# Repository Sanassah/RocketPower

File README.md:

# RocketPower

**An active fin control flight computer for model rockets.**

A model rocket built **from the ground up**: custom flight computer, custom PCB, active fin control for in-flight stabilization, and a full hardware-in-the-loop test rig.

**Status:** in bench and hardware-in-the-loop validation ahead of first flight.

---

## 🔧 Putting it together

<table><tr>
<td width="62%"></td>
<td width="38%"></td>
</tr></table>

---

## 🚀 What it does

- **Active fin control.** An ARM Cortex-M7 flight computer runs a PD controller on quaternion-derived tilt plus gyro rate, driving **4 independent servo fins** in real time for active stabilization during ascent.
- **Redundant recovery.** Apogee detection runs on multiple independent signals, each able to trigger deployment on its own.
- **Hardware-in-the-loop testing.** A custom 6DOF Simulink model drives the real flight computer over serial, so the control loop gets validated **before it ever has to fly**.
- **Custom PCB.** IMU, barometer, high-g accelerometer, GPS, power monitoring, pyro firing and continuity, and LoRa telemetry, all on one board.
- **Ground station.** A PyQt6 desktop app for live telemetry, 3D orientation, and command/control.

---

## 🧠 Architecture

Every sensor feeds one MCU; that MCU runs the active fin control law and drives every output.

```mermaid
flowchart TD
    classDef sensor fill:#4A90D9,stroke:#2C5F8A,color:#fff
    classDef compute fill:#F5A623,stroke:#B8780F,color:#000
    classDef output fill:#7ED321,stroke:#4C8A14,color:#000
    classDef ext fill:#9B59B6,stroke:#6C3483,color:#fff

    IMU[BNO085 IMU]:::sensor
    BARO[BMP390 Baro]:::sensor
    ACC[ADXL375 Accel]:::sensor
    GPS[ZOEM8 GPS]:::sensor
    PWR[INA260 Power]:::sensor

    subgraph MCU["ARM Cortex-M7 MCU (NXP i.MX RT1062)"]
        FSM[Flight State Machine]:::compute
        CTRL[PD Attitude Controller]:::compute
        PYRO[Pyro + Backup Deploy]:::compute
    end

    FINS[4x Servo Fins]:::output
    CHUTE[Recovery Parachute]:::output

    GS[GroundStation]:::ext
    SIM[Simulink 6DOF]:::ext

    IMU --> FSM
    BARO --> FSM
    ACC --> FSM
    GPS --> FSM
    PWR --> FSM
    FSM --> CTRL
    FSM --> PYRO
    CTRL --> FINS
    PYRO --> CHUTE
    FSM <-->|"LoRa, E22-900T22D"| GS
    FSM <-.->|"Serial, HITL only"| SIM

    style MCU fill:#FEF3E0,stroke:#F5A623,stroke-width:2px
```

---

## 🛠️ Hardware

Every subsystem on one custom board: IMU, barometer, high-g accelerometer, GPS, power monitoring, pyro firing/continuity, and telemetry.

---

## 🧪 Simulation and testing

Performance is modeled before anything is built, and the same model closes the loop with real hardware once it exists.

A full powered ascent, coast, and parachute deployment, run entirely in hardware-in-the-loop: **real flight computer, simulated flight.**

---

<p align="center"><sub>Where this is headed.</sub></p>

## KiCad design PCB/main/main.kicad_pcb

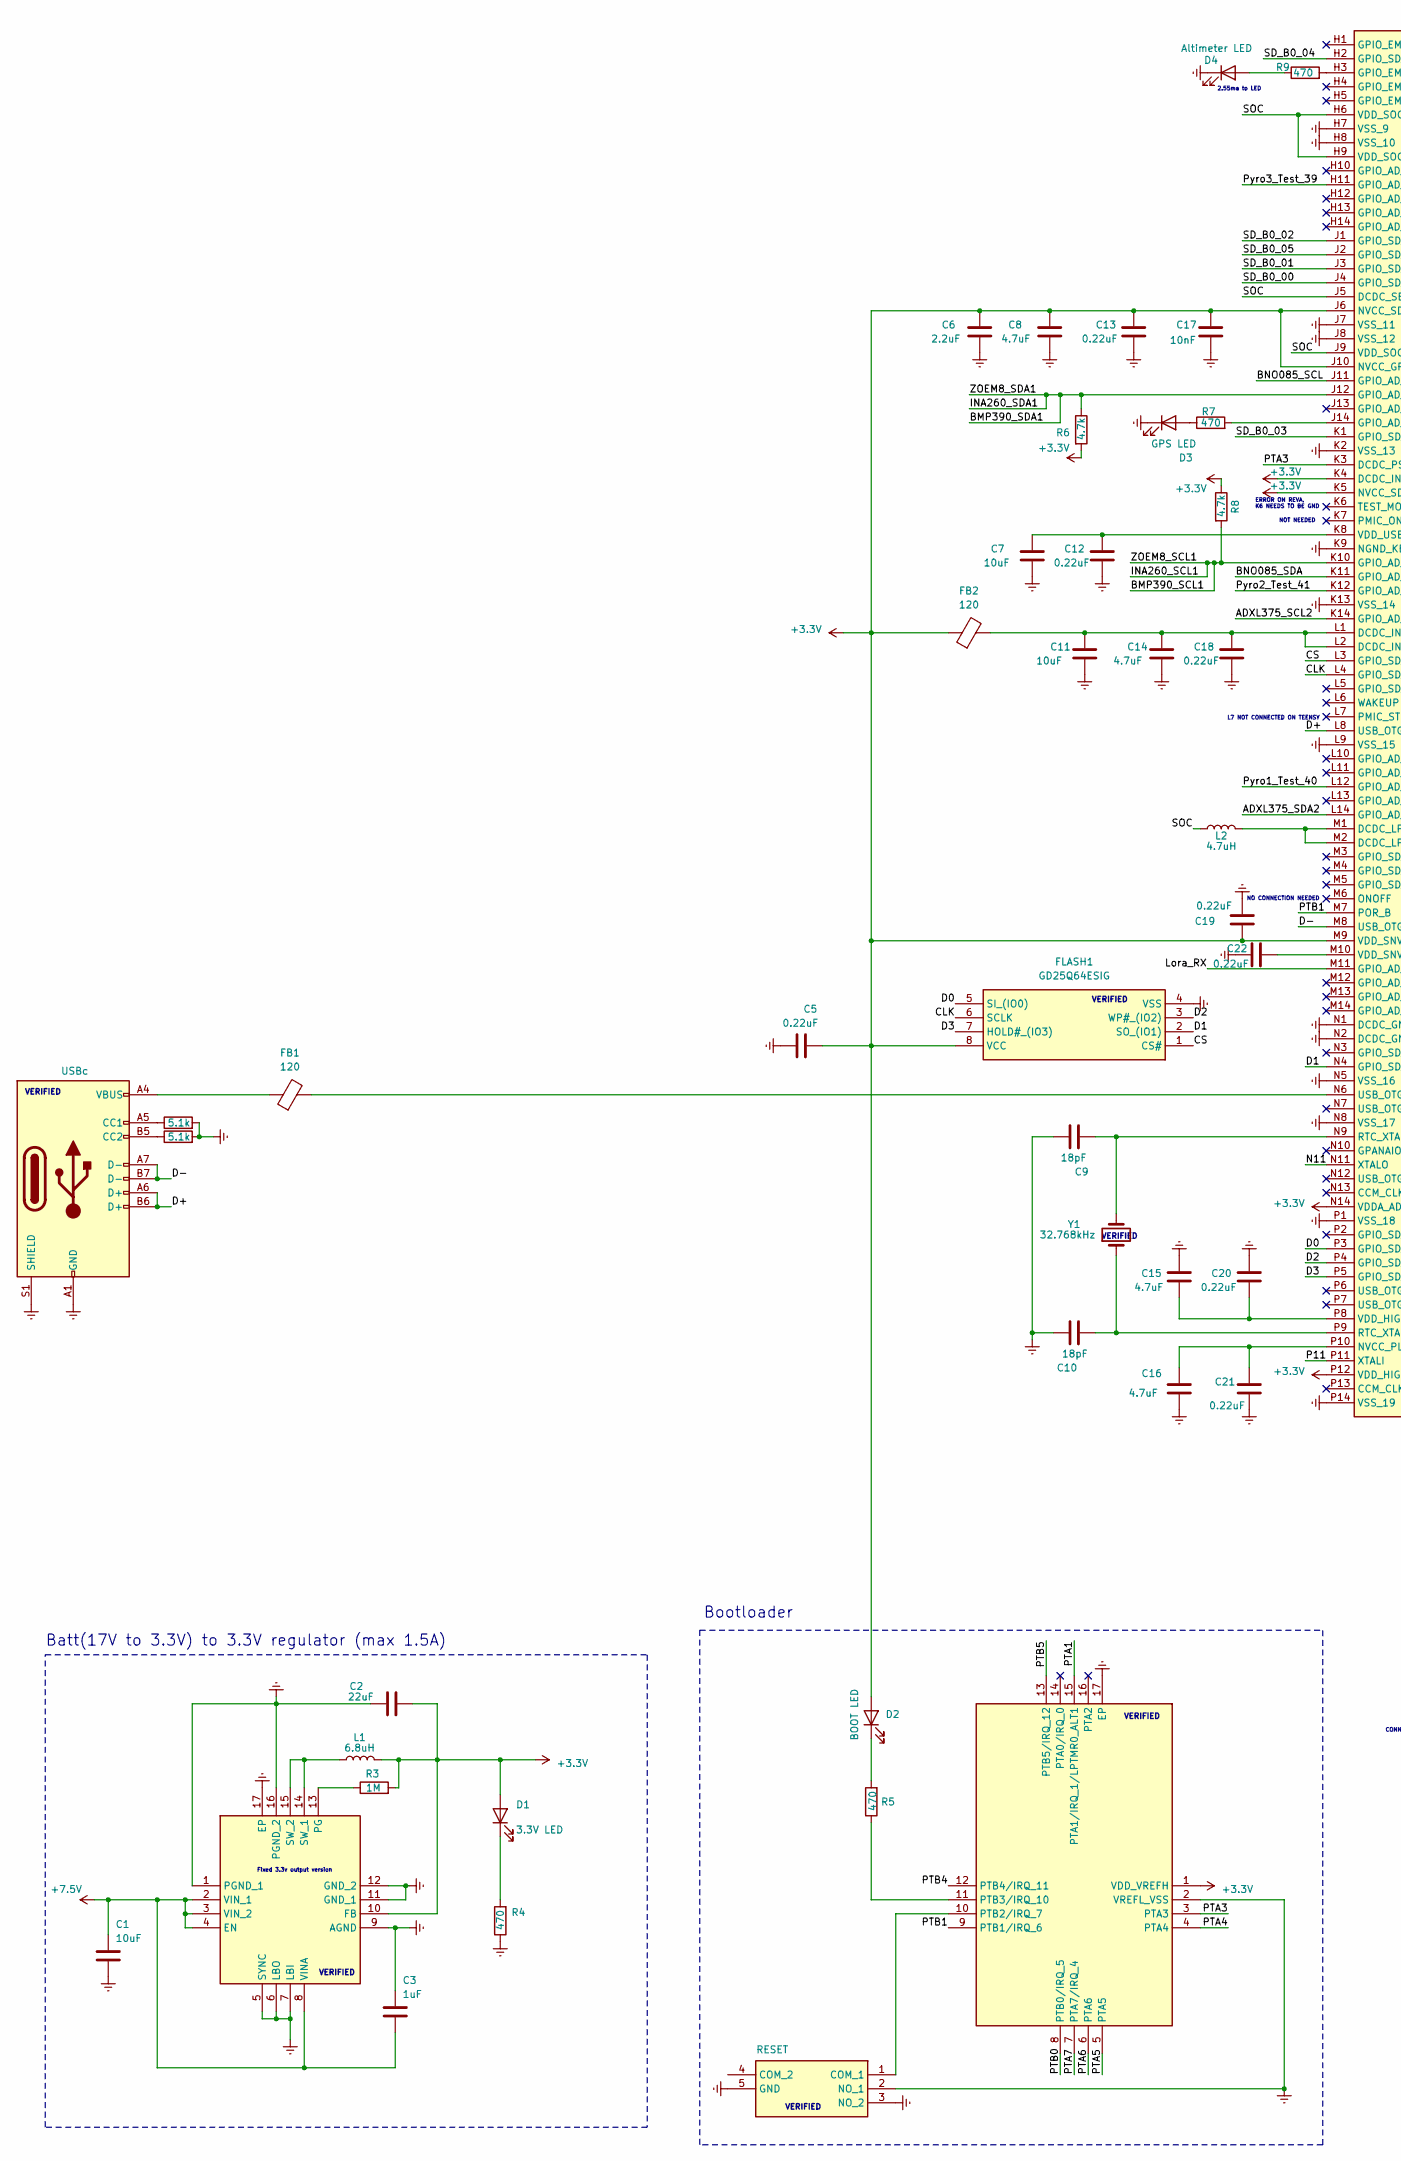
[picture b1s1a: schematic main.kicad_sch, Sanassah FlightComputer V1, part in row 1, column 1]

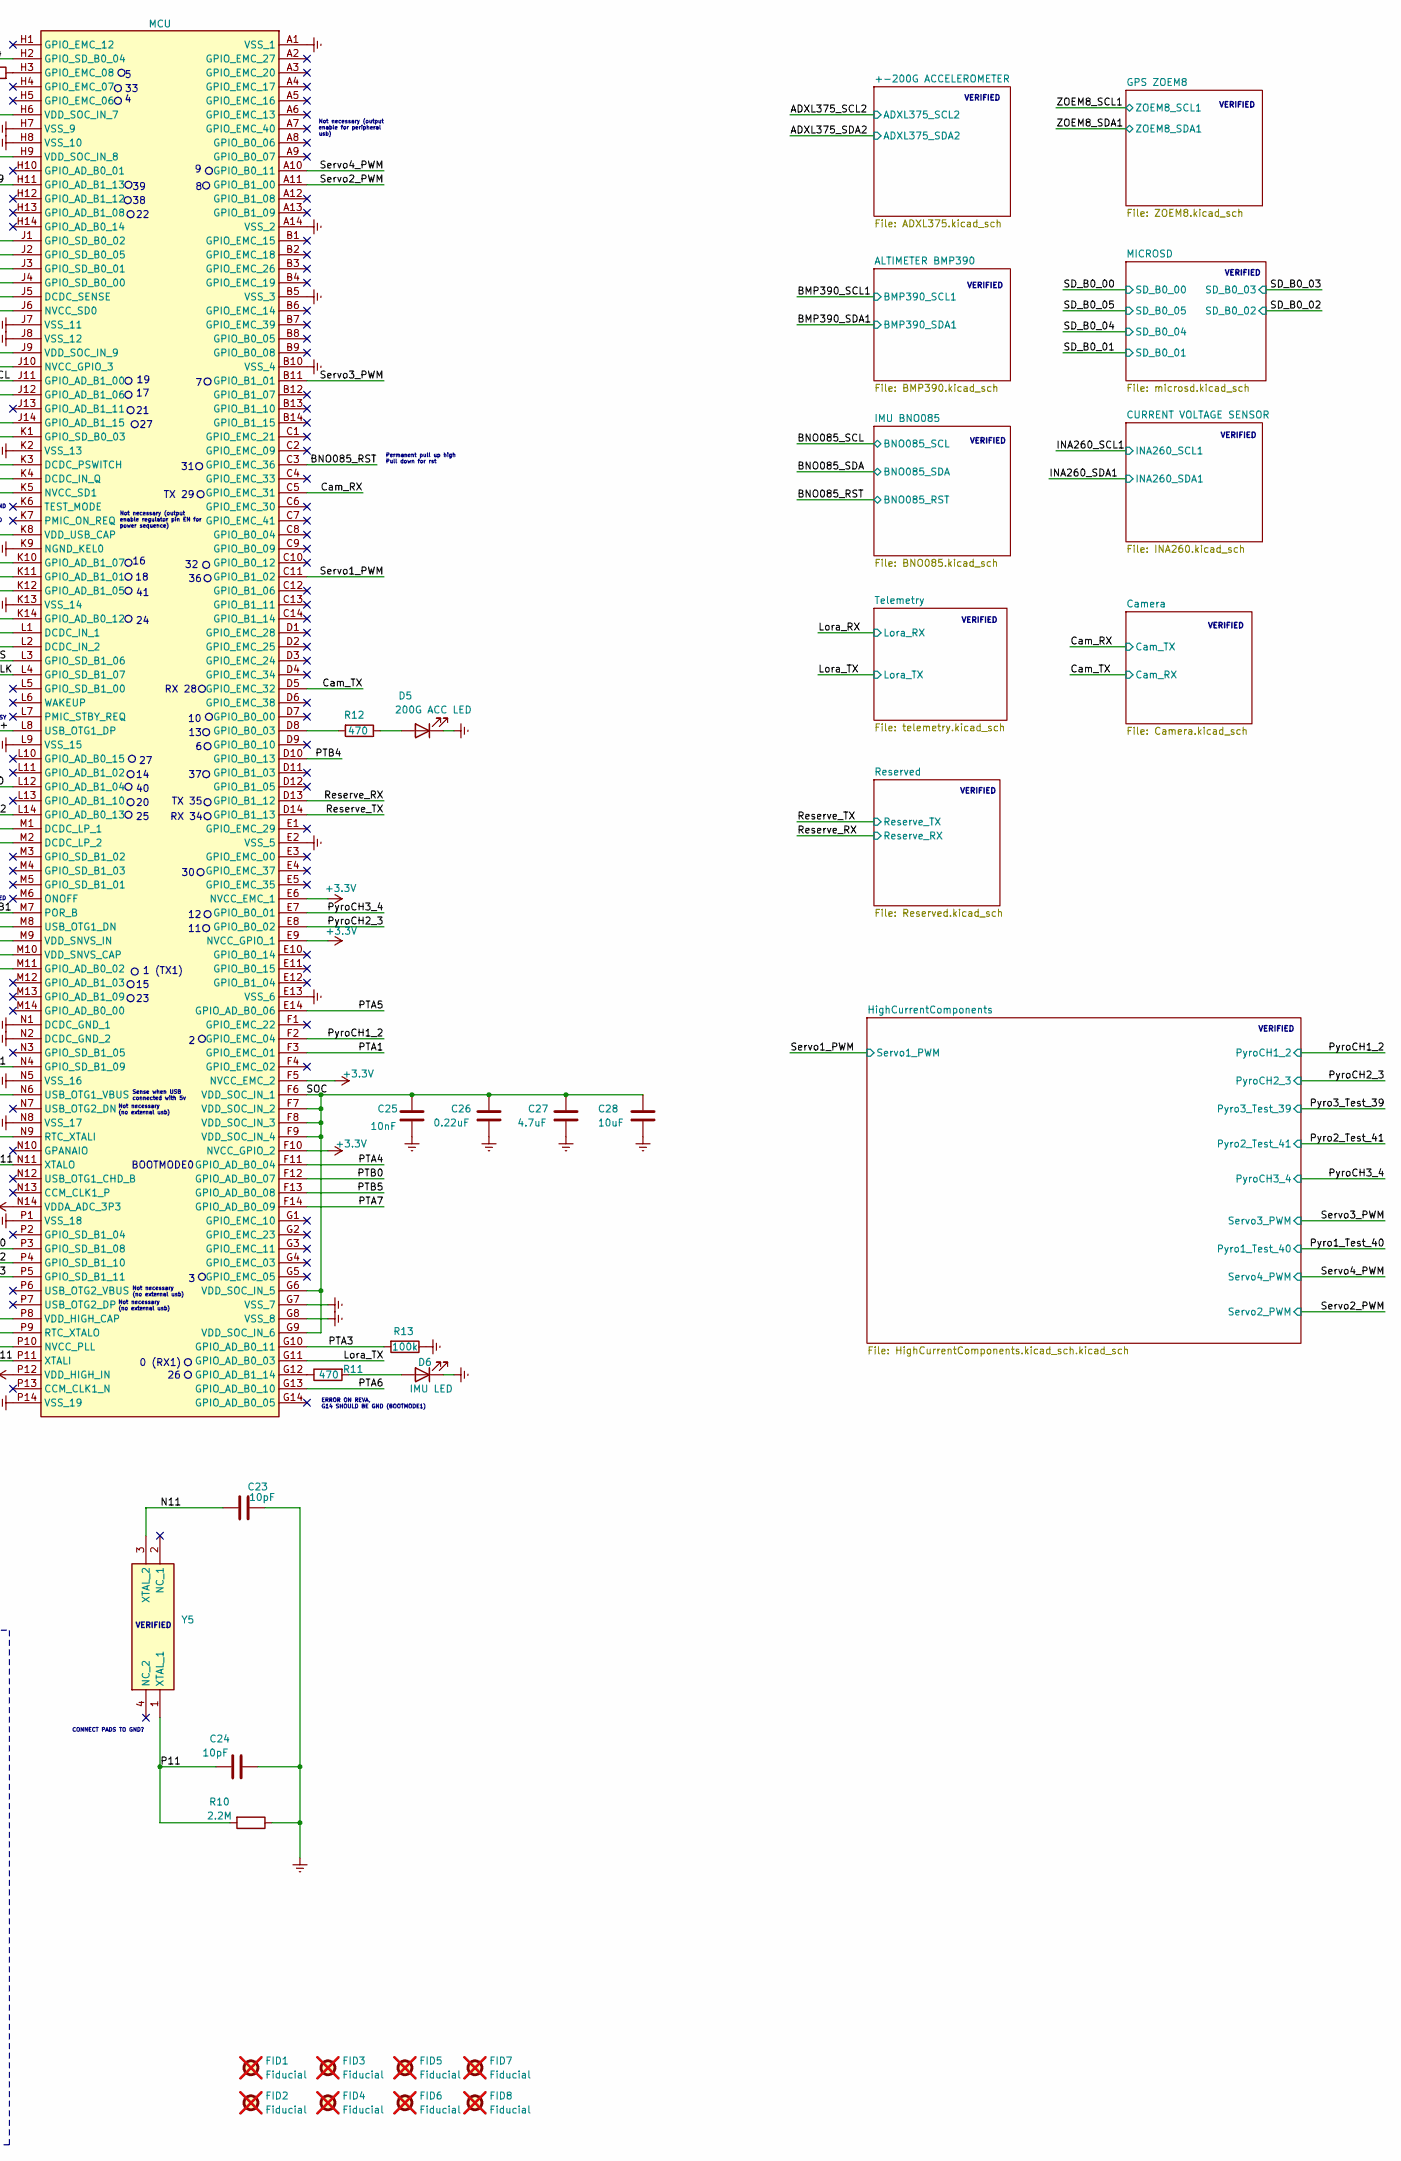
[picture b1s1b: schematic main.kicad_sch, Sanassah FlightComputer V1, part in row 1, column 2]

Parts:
C1: 10uF; R_0603_1608Metric_Pad0.98x0.95mm_HandSolder; Rating 25V; LCSC C70225
C2: 22uF; R_0603_1608Metric_Pad0.98x0.95mm_HandSolder; Rating 6.3V; LCSC C2762594
C3: 1uF; R_0603_1608Metric_Pad0.98x0.95mm_HandSolder; LCSC C1592
C5, C12, C13, C18, C19, C20, C21, C22, C26: 0.22uF; R_0603_1608Metric_Pad0.98x0.95mm_HandSolder; LCSC C106216
C6: 2.2uF; R_0603_1608Metric_Pad0.98x0.95mm_HandSolder; LCSC C23630
C7, C11, C28: 10uF; R_0603_1608Metric_Pad0.98x0.95mm_HandSolder; LCSC C70225
C8, C14, C15, C16, C27: 4.7uF; R_0603_1608Metric_Pad0.98x0.95mm_HandSolder; LCSC C19666
C9, C10: 18pF; R_0603_1608Metric_Pad0.98x0.95mm_HandSolder; LCSC C1647
C17, C25: 10nF; R_0603_1608Metric_Pad0.98x0.95mm_HandSolder; LCSC C149619
C23, C24: 10pF; R_0603_1608Metric_Pad0.98x0.95mm_HandSolder; LCSC C2168929
D1: 3.3V LED; LED_0603_1608Metric_Pad1.05x0.95mm_HandSolder; Mouser Part Number 78-TLMG1100-GS15; LCSC C20433785
D2: BOOT LED; LED_0603_1608Metric_Pad1.05x0.95mm_HandSolder; Mouser Part Number 78-TLMG1100-GS15; LCSC C20433785
D3: GPS LED; LED_0603_1608Metric_Pad1.05x0.95mm_HandSolder; Mouser Part Number 78-TLMG1100-GS15; LCSC C20433785
D4: Altimeter LED; LED_0603_1608Metric_Pad1.05x0.95mm_HandSolder; Mouser Part Number 78-TLMG1100-GS15; LCSC C20433785
D5: 200G ACC LED; LED_0603_1608Metric_Pad1.05x0.95mm_HandSolder; Mouser Part Number 78-TLMG1100-GS15; LCSC C20433785
D6: IMU LED; LED_0603_1608Metric_Pad1.05x0.95mm_HandSolder; Mouser Part Number 78-TLMG1100-GS15; LCSC C20433785
FB1, FB2: 120; R_0603_1608Metric_Pad0.98x0.95mm_HandSolder; Mouser Part Number 81-BLM18PG121SN1D; LCSC C14709
FID1, FID2, FID3, FID4, FID5, FID6, FID7, FID8: Fiducial; Fiducial_1mm_Mask2mm; not fitted
FLASH1: GD25Q64ESIG; Mouser Part Number 363-GD25Q64ESIG
KMR241GLFS1: RESET; KMR421GULCLFS; Mouser Part Number 611-KMR241GLFS
L1: 6.8uH; L_1008_2520Metric_Pad1.43x2.20mm_HandSolder; Mouser Part Number 810-VLS25212HBX6R8M1; LCSC C307868
L2: 4.7uH; L_0805_2012Metric_Pad1.05x1.20mm_HandSolder; Mouser Part Number 81-LQM21PN4R7NGRDRD; LCSC C397305
MIMXRT1062DVL6B1: MCU; BGA196C80P14X14_1200X1200X152; Manufacturer_Part_Number MIMXRT1062DVL6B; Mouser Part Number 771-MIMXRT1062DVL6B
MKL02Z32VFG1: BOOT; QFN50P300X300X65-17N-D; Manufacturer_Part_Number MKL02Z32VFG4
R1, R2: 5.1k; R_0603_1608Metric_Pad0.98x0.95mm_HandSolder; LCSC C22356467
R3: 1M; R_0603_1608Metric_Pad0.98x0.95mm_HandSolder; LCSC C22935
R4, R5, R7, R9, R11, R12: 470; R_0603_1608Metric_Pad0.98x0.95mm_HandSolder; LCSC C23179
R6, R8: 4.7k; R_0603_1608Metric_Pad0.98x0.95mm_HandSolder; LCSC C23162
R10: 2.2M; R_0603_1608Metric_Pad0.98x0.95mm_HandSolder; LCSC C18679
R13: 100k; R_0603_1608Metric_Pad0.98x0.95mm_HandSolder; LCSC C14675
TPS62111RSAR1: 3.3Vreg; TPS62111RSAR; Mouser Part Number 595-TPS62111RSAR
USB_C_Receptacle_USB2.0_14P1: USBc; USB_C_Receptacle_GCT_USB4110; Mouser Part Number 640-USB4110-GF-A; LCSC C5143397
Y1: 32.768kHz; Crystal_SMD_2012-2Pin_2.0x1.2mm_HandSoldering; Mouser Part Number 815-ABS06-32.7K-9-T; LCSC C510776
Y5: XRCGB24M000F2P29R0; XRCGB; Mouser Part Number 81-XRCGB24M000F2P29R

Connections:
+3.3V: C2.2, C5.1, C6.1, C8.1, C13.1, C17.1, C19.1, D1.2 (A), D2.2 (A), FB2.1, FLASH1.8 (VCC), L1.2, MIMXRT1062DVL6B1.E6 (NVCC_EMC_1), MIMXRT1062DVL6B1.E9 (NVCC_GPIO_1), MIMXRT1062DVL6B1.F5 (NVCC_EMC_2), MIMXRT1062DVL6B1.F10 (NVCC_GPIO_2), MIMXRT1062DVL6B1.J6 (NVCC_SD0), MIMXRT1062DVL6B1.J10 (NVCC_GPIO_3), MIMXRT1062DVL6B1.K4 (DCDC_IN_Q), MIMXRT1062DVL6B1.K5 (NVCC_SD1), MIMXRT1062DVL6B1.M9 (VDD_SNVS_IN), MIMXRT1062DVL6B1.N14 (VDDA_ADC_3P3), MIMXRT1062DVL6B1.P12 (VDD_HIGH_IN), MKL02Z32VFG1.1 (VDD_VREFH), R3.2, R6.2, R8.1, TPS62111RSAR1.10 (FB); also elsewhere on the board
+7.5V: C1.1, C3.2, TPS62111RSAR1.2 (VIN_1), TPS62111RSAR1.3 (VIN_2), TPS62111RSAR1.4 (EN), TPS62111RSAR1.8 (VINA); also elsewhere on the board
/ADXL375_SCL2: MIMXRT1062DVL6B1.K14 (GPIO_AD_B0_12); also elsewhere on the board
/ADXL375_SDA2: MIMXRT1062DVL6B1.L14 (GPIO_AD_B0_13); also elsewhere on the board
/BMP390_SCL1: MIMXRT1062DVL6B1.K10 (GPIO_AD_B1_07), R8.2; also elsewhere on the board
/BMP390_SDA1: MIMXRT1062DVL6B1.J12 (GPIO_AD_B1_06), R6.1; also elsewhere on the board
/BNO085_RST: MIMXRT1062DVL6B1.C3 (GPIO_EMC_36); also elsewhere on the board
/BNO085_SCL: MIMXRT1062DVL6B1.J11 (GPIO_AD_B1_00); also elsewhere on the board
/BNO085_SDA: MIMXRT1062DVL6B1.K11 (GPIO_AD_B1_01); also elsewhere on the board
/CLK: FLASH1.6 (SCLK), MIMXRT1062DVL6B1.L4 (GPIO_SD_B1_07)
/CS: FLASH1.1 (CS#), MIMXRT1062DVL6B1.L3 (GPIO_SD_B1_06)
/Cam_RX: MIMXRT1062DVL6B1.C5 (GPIO_EMC_31); also elsewhere on the board
/Cam_TX: MIMXRT1062DVL6B1.D5 (GPIO_EMC_32); also elsewhere on the board
/D0: FLASH1.5 (SI_(IO0)), MIMXRT1062DVL6B1.P3 (GPIO_SD_B1_08)
/D1: FLASH1.2 (SO_(IO1)), MIMXRT1062DVL6B1.N4 (GPIO_SD_B1_09)
/D2: FLASH1.3 (WP#_(IO2)), MIMXRT1062DVL6B1.P4 (GPIO_SD_B1_10)
/D3: FLASH1.7 (HOLD#_(IO3)), MIMXRT1062DVL6B1.P5 (GPIO_SD_B1_11)
/D+: MIMXRT1062DVL6B1.L8 (USB_OTG1_DP), USB_C_Receptacle_USB2.0_14P1.A6 (D+), USB_C_Receptacle_USB2.0_14P1.B6 (D+)
/D-: MIMXRT1062DVL6B1.M8 (USB_OTG1_DN), USB_C_Receptacle_USB2.0_14P1.A7 (D-), USB_C_Receptacle_USB2.0_14P1.B7 (D-)
/Lora_RX: MIMXRT1062DVL6B1.M11 (GPIO_AD_B0_02); also elsewhere on the board
/Lora_TX: MIMXRT1062DVL6B1.G11 (GPIO_AD_B0_03); also elsewhere on the board
/N11: C23.1, MIMXRT1062DVL6B1.N11 (XTALO), Y5.3 (XTAL_2)
/P11: C24.2, MIMXRT1062DVL6B1.P11 (XTALI), R10.2, Y5.1 (XTAL_1)
/PTA1: MIMXRT1062DVL6B1.F3 (GPIO_EMC_01), MKL02Z32VFG1.15 (PTA1/IRQ_1/LPTMR0_ALT1)
/PTA3: MIMXRT1062DVL6B1.G10 (GPIO_AD_B0_11), MIMXRT1062DVL6B1.K3 (DCDC_PSWITCH), MKL02Z32VFG1.3 (PTA3), R13.2
/PTA4: MIMXRT1062DVL6B1.F11 (GPIO_AD_B0_04), MKL02Z32VFG1.4 (PTA4)
/PTA5: MIMXRT1062DVL6B1.E14 (GPIO_AD_B0_06), MKL02Z32VFG1.5 (PTA5)
/PTA6: MIMXRT1062DVL6B1.G13 (GPIO_AD_B0_10), MKL02Z32VFG1.6 (PTA6)
/PTA7: MIMXRT1062DVL6B1.F14 (GPIO_AD_B0_09), MKL02Z32VFG1.7 (PTA7/IRQ_4)
/PTB0: MIMXRT1062DVL6B1.F12 (GPIO_AD_B0_07), MKL02Z32VFG1.8 (PTB0/IRQ_5)
/PTB1: MIMXRT1062DVL6B1.M7 (POR_B), MKL02Z32VFG1.9 (PTB1/IRQ_6)
/PTB4: MIMXRT1062DVL6B1.D10 (GPIO_B0_13), MKL02Z32VFG1.12 (PTB4/IRQ_11)
/PTB5: MIMXRT1062DVL6B1.F13 (GPIO_AD_B0_08), MKL02Z32VFG1.13 (PTB5/IRQ_12)
/Pyro1_Test_40: MIMXRT1062DVL6B1.L12 (GPIO_AD_B1_04); also elsewhere on the board
/Pyro2_Test_41: MIMXRT1062DVL6B1.K12 (GPIO_AD_B1_05); also elsewhere on the board
/Pyro3_Test_39: MIMXRT1062DVL6B1.H11 (GPIO_AD_B1_13); also elsewhere on the board
/PyroCH1_2: MIMXRT1062DVL6B1.F2 (GPIO_EMC_04); also elsewhere on the board
/PyroCH2_3: MIMXRT1062DVL6B1.E8 (GPIO_B0_02); also elsewhere on the board
/PyroCH3_4: MIMXRT1062DVL6B1.E7 (GPIO_B0_01); also elsewhere on the board
/Reserve_RX: MIMXRT1062DVL6B1.D13 (GPIO_B1_12); also elsewhere on the board
/Reserve_TX: MIMXRT1062DVL6B1.D14 (GPIO_B1_13); also elsewhere on the board
/SD_B0_00: MIMXRT1062DVL6B1.J4 (GPIO_SD_B0_00); also elsewhere on the board
/SD_B0_01: MIMXRT1062DVL6B1.J3 (GPIO_SD_B0_01); also elsewhere on the board
/SD_B0_02: MIMXRT1062DVL6B1.J1 (GPIO_SD_B0_02); also elsewhere on the board
/SD_B0_03: MIMXRT1062DVL6B1.K1 (GPIO_SD_B0_03); also elsewhere on the board
/SD_B0_04: MIMXRT1062DVL6B1.H2 (GPIO_SD_B0_04); also elsewhere on the board
/SD_B0_05: MIMXRT1062DVL6B1.J2 (GPIO_SD_B0_05); also elsewhere on the board
/SOC: C25.1, C26.1, C27.1, C28.1, L2.2, MIMXRT1062DVL6B1.F6 (VDD_SOC_IN_1), MIMXRT1062DVL6B1.F7 (VDD_SOC_IN_2), MIMXRT1062DVL6B1.F8 (VDD_SOC_IN_3), MIMXRT1062DVL6B1.F9 (VDD_SOC_IN_4), MIMXRT1062DVL6B1.G6 (VDD_SOC_IN_5), MIMXRT1062DVL6B1.G9 (VDD_SOC_IN_6), MIMXRT1062DVL6B1.H6 (VDD_SOC_IN_7), MIMXRT1062DVL6B1.H9 (VDD_SOC_IN_8), MIMXRT1062DVL6B1.J5 (DCDC_SENSE), MIMXRT1062DVL6B1.J9 (VDD_SOC_IN_9)
/Servo1_PWM: MIMXRT1062DVL6B1.C11 (GPIO_B1_02); also elsewhere on the board
/Servo2_PWM: MIMXRT1062DVL6B1.A11 (GPIO_B1_00); also elsewhere on the board
/Servo3_PWM: MIMXRT1062DVL6B1.B11 (GPIO_B1_01); also elsewhere on the board
/Servo4_PWM: MIMXRT1062DVL6B1.A10 (GPIO_B0_11); also elsewhere on the board
GNDREF: C1.2, C2.1, C3.1, C5.2, C6.2, C7.2, C8.2, C9.2, C10.1, C11.2, C12.2, C13.2, C14.2, C15.2, C16.2, C17.2, C18.2, C19.2, C20.2, C21.2, C22.1, C23.2, C24.1, C25.2, C26.2, C27.2, C28.2, D3.1 (K), D4.1 (K), D5.1 (K), D6.1 (K), FLASH1.4 (VSS), KMR241GLFS1.2 (NO_1), KMR241GLFS1.3 (NO_2), KMR241GLFS1.5 (GND), MIMXRT1062DVL6B1.A1 (VSS_1), MIMXRT1062DVL6B1.A14 (VSS_2), MIMXRT1062DVL6B1.B5 (VSS_3), MIMXRT1062DVL6B1.B10 (VSS_4), MIMXRT1062DVL6B1.E2 (VSS_5), MIMXRT1062DVL6B1.E13 (VSS_6), MIMXRT1062DVL6B1.G7 (VSS_7), MIMXRT1062DVL6B1.G8 (VSS_8), MIMXRT1062DVL6B1.H7 (VSS_9), MIMXRT1062DVL6B1.H8 (VSS_10), MIMXRT1062DVL6B1.J7 (VSS_11), MIMXRT1062DVL6B1.J8 (VSS_12), MIMXRT1062DVL6B1.K2 (VSS_13), MIMXRT1062DVL6B1.K9 (NGND_KEL0), MIMXRT1062DVL6B1.K13 (VSS_14), MIMXRT1062DVL6B1.L9 (VSS_15), MIMXRT1062DVL6B1.N1 (DCDC_GND_1), MIMXRT1062DVL6B1.N2 (DCDC_GND_2), MIMXRT1062DVL6B1.N5 (VSS_16), MIMXRT1062DVL6B1.N8 (VSS_17), MIMXRT1062DVL6B1.P1 (VSS_18), MIMXRT1062DVL6B1.P14 (VSS_19), MKL02Z32VFG1.2 (VREFL_VSS), MKL02Z32VFG1.17 (EP), R1.2, R2.2, R4.1, R10.1, R13.1, TPS62111RSAR1.1 (PGND_1), TPS62111RSAR1.5 (SYNC), TPS62111RSAR1.6 (LBO), TPS62111RSAR1.7 (LBI), TPS62111RSAR1.9 (AGND), TPS62111RSAR1.11 (GND_1), TPS62111RSAR1.12 (GND_2), TPS62111RSAR1.16 (PGND_2), TPS62111RSAR1.17 (EP), USB_C_Receptacle_USB2.0_14P1.A1 (GND), USB_C_Receptacle_USB2.0_14P1.A12 (GND), USB_C_Receptacle_USB2.0_14P1.B1 (GND), USB_C_Receptacle_USB2.0_14P1.B12 (GND), USB_C_Receptacle_USB2.0_14P1.S1 (SHIELD); also elsewhere on the board
unnamed: D1.1 (K), R4.2
unnamed: D2.1 (K), R5.2
unnamed: D3.2 (A), R7.1
unnamed: D4.2 (A), R9.1
unnamed: D5.2 (A), R12.1
unnamed: D6.2 (A), R11.2
unnamed: FB1.1, USB_C_Receptacle_USB2.0_14P1.A4 (VBUS), USB_C_Receptacle_USB2.0_14P1.A9 (VBUS), USB_C_Receptacle_USB2.0_14P1.B4 (VBUS), USB_C_Receptacle_USB2.0_14P1.B9 (VBUS)
unnamed: KMR241GLFS1.1 (COM_1), MKL02Z32VFG1.10 (PTB2/IRQ_7)
unnamed: C11.1, C14.1, C18.1, FB2.2, MIMXRT1062DVL6B1.L1 (DCDC_IN_1), MIMXRT1062DVL6B1.L2 (DCDC_IN_2)
unnamed: L2.1, MIMXRT1062DVL6B1.M1 (DCDC_LP_1), MIMXRT1062DVL6B1.M2 (DCDC_LP_2)
unnamed: MIMXRT1062DVL6B1.G12 (GPIO_AD_B1_14), R11.1
unnamed: MIMXRT1062DVL6B1.J14 (GPIO_AD_B1_15), R7.2
unnamed: MIMXRT1062DVL6B1.D8 (GPIO_B0_03), R12.2
unnamed: MIMXRT1062DVL6B1.H3 (GPIO_EMC_08), R9.2
unnamed: C16.1, C21.1, MIMXRT1062DVL6B1.P10 (NVCC_PLL)
unnamed: C9.1, MIMXRT1062DVL6B1.N9 (RTC_XTALI), Y1.2
unnamed: C10.2, MIMXRT1062DVL6B1.P9 (RTC_XTALO), Y1.1
unnamed: FB1.2, MIMXRT1062DVL6B1.N6 (USB_OTG1_VBUS)
unnamed: C15.1, C20.1, MIMXRT1062DVL6B1.P8 (VDD_HIGH_CAP)
unnamed: C22.2, MIMXRT1062DVL6B1.M10 (VDD_SNVS_CAP)
unnamed: C7.1, C12.1, MIMXRT1062DVL6B1.K8 (VDD_USB_CAP)
unnamed: MKL02Z32VFG1.11 (PTB3/IRQ_10), R5.1
unnamed: R3.1, TPS62111RSAR1.13 (PG)
unnamed: L1.1, TPS62111RSAR1.14 (SW_1), TPS62111RSAR1.15 (SW_2)
unnamed: R1.1, USB_C_Receptacle_USB2.0_14P1.A5 (CC1)
unnamed: R2.1, USB_C_Receptacle_USB2.0_14P1.B5 (CC2)

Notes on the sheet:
VERIFIED
0 (RX1)
2.55ma to LED
Not necessary (no external usb)
Batt(17V to 3.3V) to 3.3V regulator (max 1.5A)
Not necessary (output enable regulator pin EN for power sequence)
Not necessary (output enable for peripheral usb)
TX 29
L7 NOT CONNECTED ON TEENSY
NO CONNECTION NEEDED
ERROR ON REVA, K6 NEEDS TO BE GND
1 (TX1)
TX 35
CONNECT PADS TO GND?
Permanent pull up high Pull down for rst
RX 34
ERROR ON REVA, G14 SHOULD BE GND (BOOTMODE1)
Sense when USB connected with 5v
Fixed 3.3v output version
BOOTMODE0
NOT NEEDED
Bootloader
RX 28

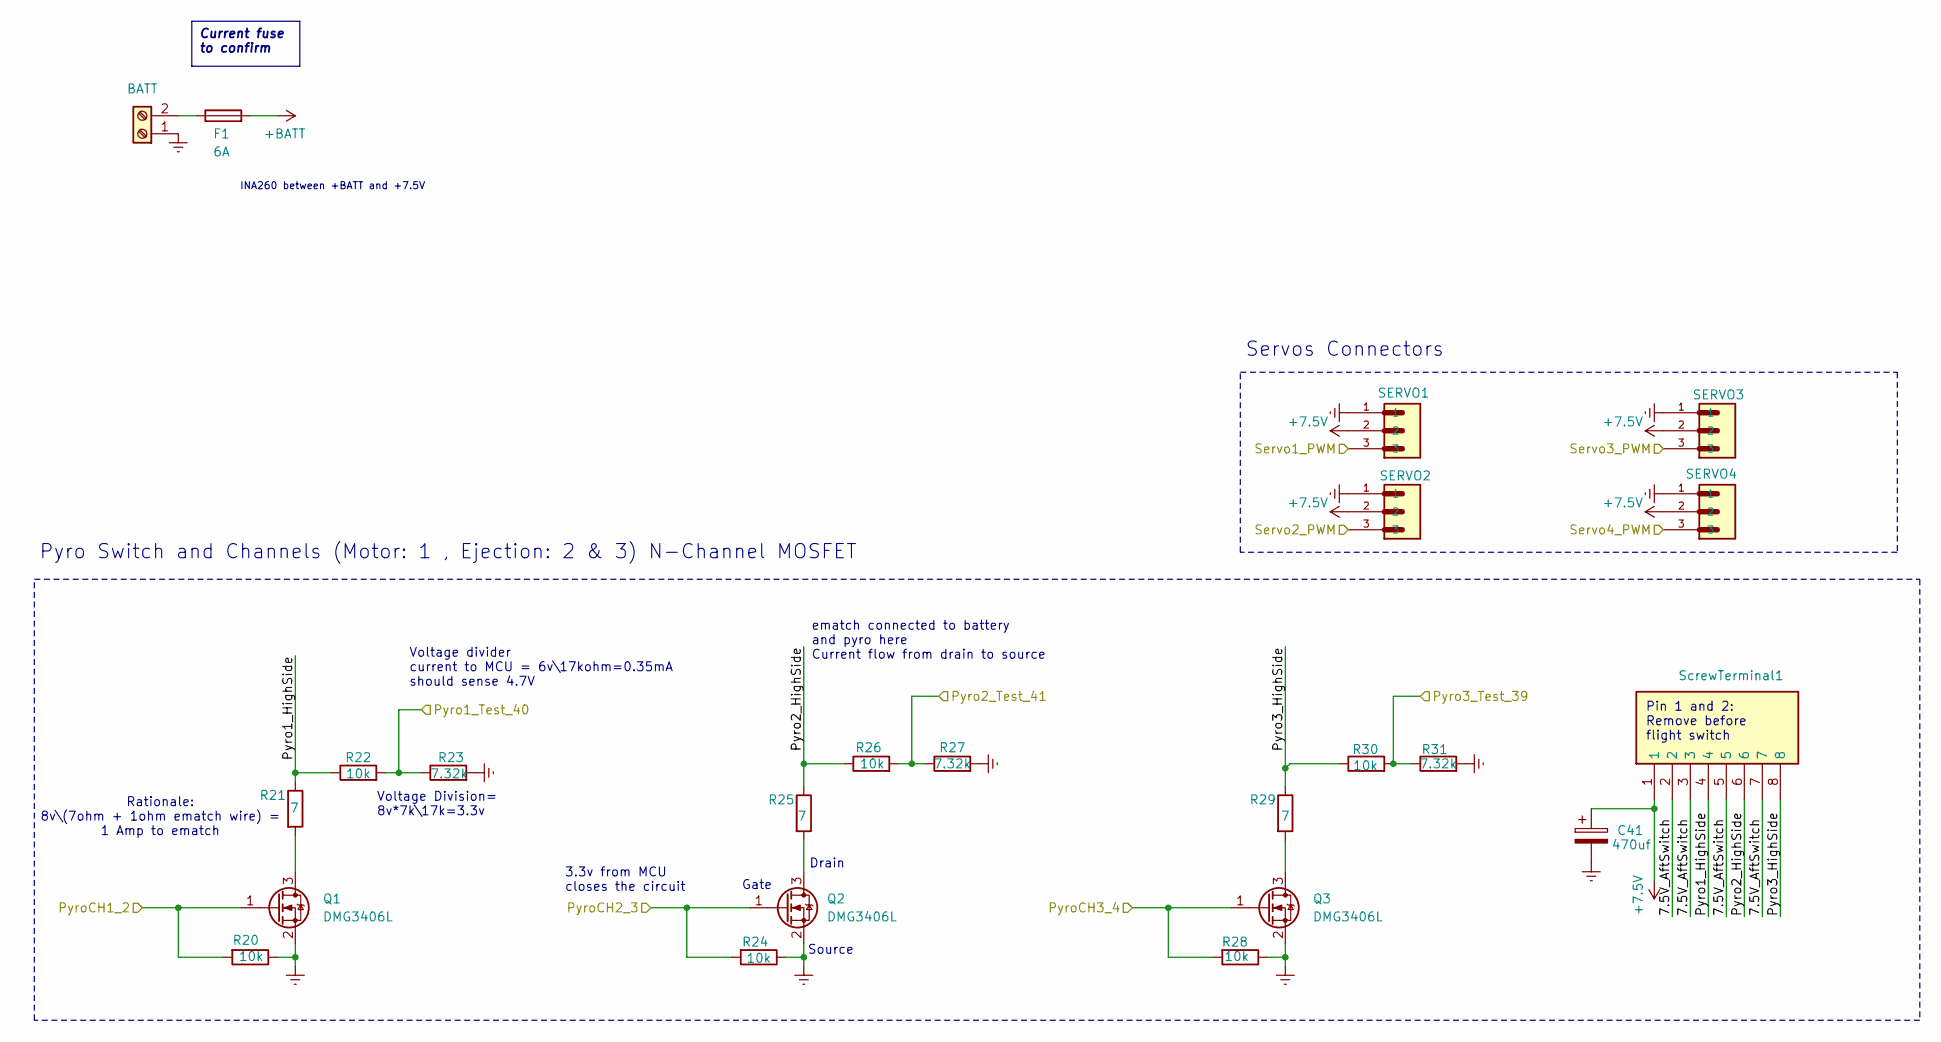
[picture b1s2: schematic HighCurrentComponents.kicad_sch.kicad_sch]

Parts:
C41: 470uf; C_Radial_D6.3mm_H11.0mm_P2.50mm; LCSC C1020067
F1: 6A; Fuse_1206_3216Metric; Mouser Part Number 530-C1F6; LCSC C183157
Q1, Q2, Q3: DMG3406L; SOT-23; Mouser Part Number 621-DMG3406L-7; LCSC C460978
R20, R22, R24, R26, R28, R30: 10k; R_0603_1608Metric_Pad0.98x0.95mm_HandSolder; LCSC C25804
R21, R25, R29: 7; R_0603_1608Metric_Pad0.98x0.95mm_HandSolder; LCSC C228062
R23, R27, R31: 7.32k; R_0603_1608Metric_Pad0.98x0.95mm_HandSolder; LCSC C23101
SERVO1: SERVO1; JST_GH_BM03B-GHS-TBT_1x03-1MP_P1.25mm_Vertical; Mouser Part Number 306-BM03BGHSTBTLFSNN; LCSC C161691
SERVO2: SERVO2; JST_GH_BM03B-GHS-TBT_1x03-1MP_P1.25mm_Vertical; Mouser Part Number 306-BM03BGHSTBTLFSNN; LCSC C161691
SERVO3: SERVO3; JST_GH_BM03B-GHS-TBT_1x03-1MP_P1.25mm_Vertical; Mouser Part Number 306-BM03BGHSTBTLFSNN; LCSC C161691
SERVO4: SERVO4; JST_GH_BM03B-GHS-TBT_1x03-1MP_P1.25mm_Vertical; Mouser Part Number 306-BM03BGHSTBTLFSNN; LCSC C161691
ScrewTerminal1: 1725711; Mouser Part Number 651-1725711
ScrewTerminal2: BATT; 1725656; Mouser Part Number 651-1725656; LCSC C3029316

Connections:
+7.5V: C41.1, SERVO1.2, SERVO2.2, SERVO3.2, SERVO4.2, ScrewTerminal1.1; also elsewhere on the board
+BATT: F1.2; also elsewhere on the board
/HighCurrentComponents/7.5V_AftSwitch: ScrewTerminal1.2, ScrewTerminal1.3, ScrewTerminal1.5, ScrewTerminal1.7
/HighCurrentComponents/Pyro1_HighSide: R21.1, R22.1, ScrewTerminal1.4
/HighCurrentComponents/Pyro2_HighSide: R25.1, R26.1, ScrewTerminal1.6
/HighCurrentComponents/Pyro3_HighSide: R29.1, R30.1, ScrewTerminal1.8
/Pyro1_Test_40: R22.2, R23.1; also elsewhere on the board
/Pyro2_Test_41: R26.2, R27.1; also elsewhere on the board
/Pyro3_Test_39: R30.2, R31.1; also elsewhere on the board
/PyroCH1_2: Q1.1 (G), R20.2; also elsewhere on the board
/PyroCH2_3: Q2.1 (G), R24.2; also elsewhere on the board
/PyroCH3_4: Q3.1 (G), R28.2; also elsewhere on the board
/Servo1_PWM: SERVO1.3; also elsewhere on the board
/Servo2_PWM: SERVO2.3; also elsewhere on the board
/Servo3_PWM: SERVO3.3; also elsewhere on the board
/Servo4_PWM: SERVO4.3; also elsewhere on the board
GNDREF: C41.2, Q1.2 (S), Q2.2 (S), Q3.2 (S), R20.1, R23.2, R24.1, R27.2, R28.1, R31.2, SERVO1.1, SERVO2.1, SERVO3.1, SERVO4.1, ScrewTerminal2.1; also elsewhere on the board
unnamed: Q1.3 (D), R21.2
unnamed: Q2.3 (D), R25.2
unnamed: Q3.3 (D), R29.2
unnamed: F1.1, ScrewTerminal2.2

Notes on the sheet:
Voltage Division= 8v*7k\17k=3.3v
INA260 between +BATT and +7.5V
Source
Servos Connectors
Voltage divider current to MCU = 6v\17kohm=0.35mA should sense 4.7V
Pin 1 and 2: Remove before flight switch
Drain
Pyro Switch and Channels (Motor: 1 , Ejection: 2 & 3) N-Channel MOSFET
Rationale: 8v\(7ohm + 1ohm ematch wire) = 1 Amp to ematch
ematch connected to battery and pyro here Current flow from drain to source
Gate
3.3v from MCU closes the circuit
Current fuse to confirm

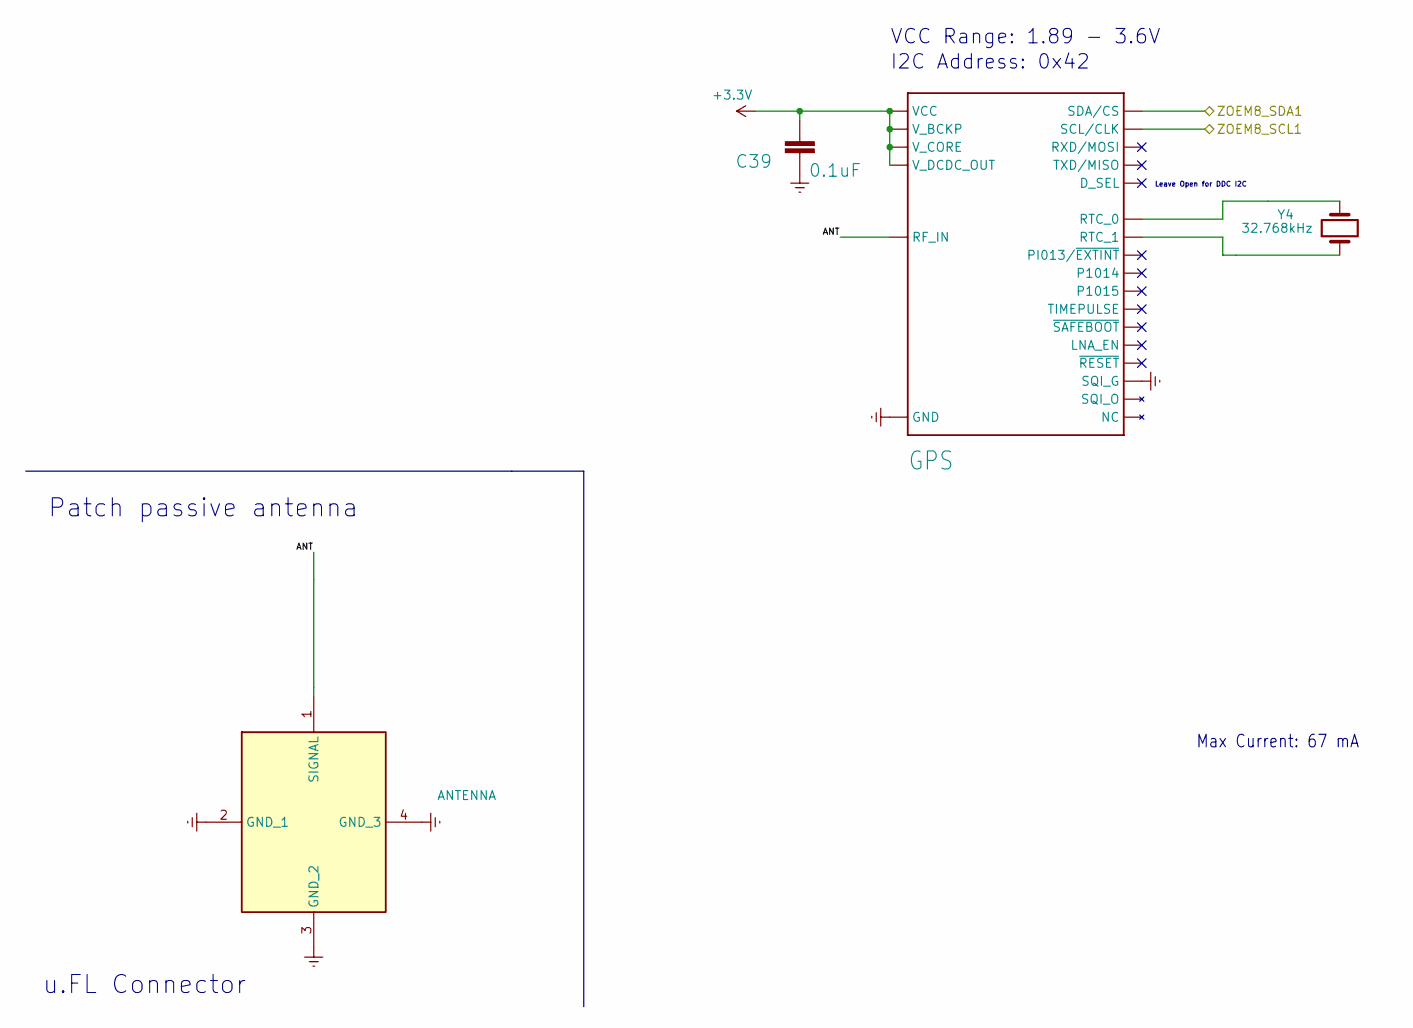
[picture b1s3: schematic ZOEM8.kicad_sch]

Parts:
C39: 0.1uF; R_0603_1608Metric_Pad0.98x0.95mm_HandSolder; LCSC C1590
CONMHF1-SMD-G-T1: ANTENNA; CONMHF1SMDGT; Mouser Part Number 712-CONMHF1-SMD-G-T
U-BLOX_ZOE_M8Q-0-1: GPS; UBLOX_ZOE_M8-0-10; Mouser Part Number 377-ZOE-M8Q-0
Y4: 32.768kHz; 830050789; Mouser Part Number 428-202816-MC01; LCSC C7462219

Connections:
+3.3V: C39.1, U-BLOX_ZOE_M8Q-0-1.16 (V_BCKP), U-BLOX_ZOE_M8Q-0-1.24 (VCC), U-BLOX_ZOE_M8Q-0-1.25 (VCC), U-BLOX_ZOE_M8Q-0-1.26 (V_DCDC_OUT), U-BLOX_ZOE_M8Q-0-1.27 (V_CORE); also elsewhere on the board
/BMP390_SCL1: U-BLOX_ZOE_M8Q-0-1.32 (SCL/CLK); also elsewhere on the board
/BMP390_SDA1: U-BLOX_ZOE_M8Q-0-1.2 (SDA/CS); also elsewhere on the board
/GPS ZOEM8/ANT: CONMHF1-SMD-G-T1.1 (SIGNAL), U-BLOX_ZOE_M8Q-0-1.4 (RF_IN)
GNDREF: C39.2, CONMHF1-SMD-G-T1.2 (GND_1), CONMHF1-SMD-G-T1.3 (GND_2), CONMHF1-SMD-G-T1.4 (GND_3), U-BLOX_ZOE_M8Q-0-1.1 (GND), U-BLOX_ZOE_M8Q-0-1.3 (GND), U-BLOX_ZOE_M8Q-0-1.5 (GND), U-BLOX_ZOE_M8Q-0-1.7 (GND), U-BLOX_ZOE_M8Q-0-1.8 (GND), U-BLOX_ZOE_M8Q-0-1.9 (GND), U-BLOX_ZOE_M8Q-0-1.10 (GND), U-BLOX_ZOE_M8Q-0-1.11 (GND), U-BLOX_ZOE_M8Q-0-1.12 (GND), U-BLOX_ZOE_M8Q-0-1.17 (GND), U-BLOX_ZOE_M8Q-0-1.23 (GND), U-BLOX_ZOE_M8Q-0-1.29 (SQI_G), U-BLOX_ZOE_M8Q-0-1.31 (SQI_G), U-BLOX_ZOE_M8Q-0-1.37 (GND), U-BLOX_ZOE_M8Q-0-1.38 (GND), U-BLOX_ZOE_M8Q-0-1.39 (GND), U-BLOX_ZOE_M8Q-0-1.40 (GND), U-BLOX_ZOE_M8Q-0-1.41 (GND), U-BLOX_ZOE_M8Q-0-1.44 (GND), U-BLOX_ZOE_M8Q-0-1.46 (SQI_G), U-BLOX_ZOE_M8Q-0-1.47 (SQI_G), U-BLOX_ZOE_M8Q-0-1.49 (GND); also elsewhere on the board
unnamed: U-BLOX_ZOE_M8Q-0-1.18 (RTC_0), Y4.2
unnamed: U-BLOX_ZOE_M8Q-0-1.19 (RTC_1), Y4.1

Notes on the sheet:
I2C Address: 0x42
VCC Range: 1.89 - 3.6V
Max Current: 67 mA
u.FL Connector
Patch passive antenna
Leave Open for DDC I2C

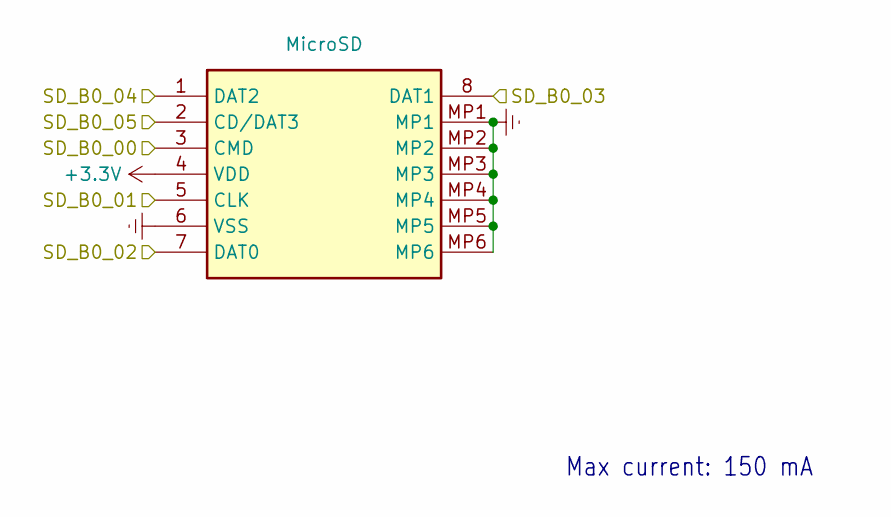
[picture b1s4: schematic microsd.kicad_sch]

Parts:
DM3D-SF1: MicroSD; DM3DSF; Mouser Part Number 798-DM3D-SF

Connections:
+3.3V: DM3D-SF1.4 (VDD); also elsewhere on the board
/SD_B0_00: DM3D-SF1.3 (CMD); also elsewhere on the board
/SD_B0_01: DM3D-SF1.5 (CLK); also elsewhere on the board
/SD_B0_02: DM3D-SF1.7 (DAT0); also elsewhere on the board
/SD_B0_03: DM3D-SF1.8 (DAT1); also elsewhere on the board
/SD_B0_04: DM3D-SF1.1 (DAT2); also elsewhere on the board
/SD_B0_05: DM3D-SF1.2 (CD/DAT3); also elsewhere on the board
GNDREF: DM3D-SF1.6 (VSS), DM3D-SF1.MP1, DM3D-SF1.MP2, DM3D-SF1.MP3, DM3D-SF1.MP4, DM3D-SF1.MP5, DM3D-SF1.MP6; also elsewhere on the board

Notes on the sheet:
Max current: 150 mA

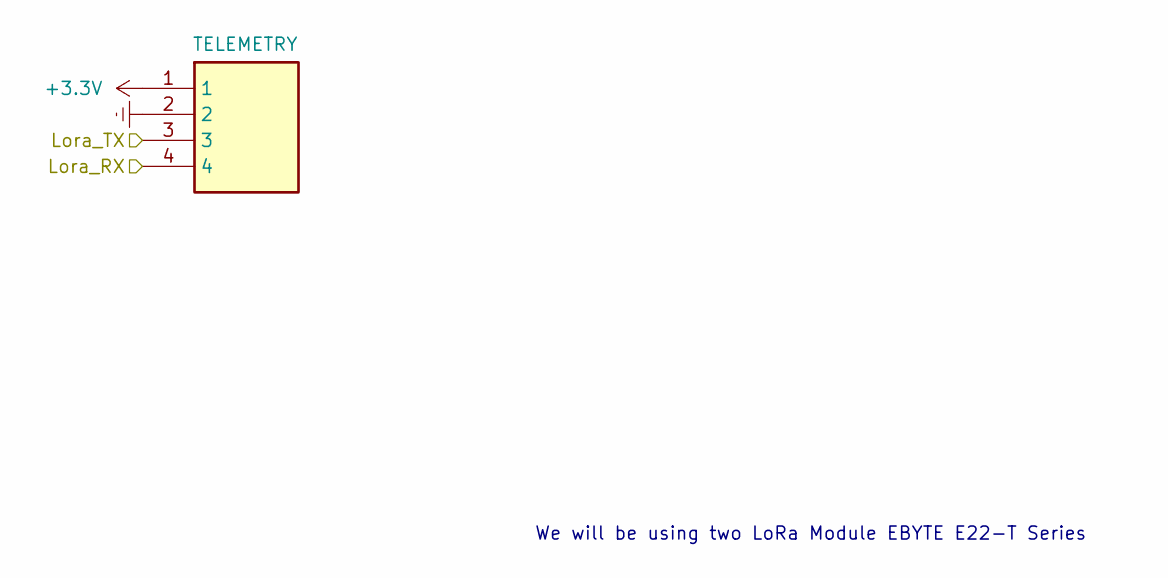
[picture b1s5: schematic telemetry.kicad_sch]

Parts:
JST-GH-1: TELEMETRY; JST_GH_BM04B-GHS-TBT_1x04-1MP_P1.25mm_Vertical; Mouser Part Number 306-BM04BGHSTBTLFSNN

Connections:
+3.3V: JST-GH-1.1; also elsewhere on the board
/Lora_RX: JST-GH-1.4; also elsewhere on the board
/Lora_TX: JST-GH-1.3; also elsewhere on the board
GNDREF: JST-GH-1.2; also elsewhere on the board

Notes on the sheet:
We will be using two LoRa Module EBYTE E22-T Series

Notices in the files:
parts and their libraries:
Copyright 2016 Accelerated Designs. All rights reserved.
